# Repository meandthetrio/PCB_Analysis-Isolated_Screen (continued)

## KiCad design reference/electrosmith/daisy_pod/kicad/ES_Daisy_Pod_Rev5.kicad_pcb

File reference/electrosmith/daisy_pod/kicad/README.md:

Converted from `../ES_Daisy_Pod_Rev5.brd` (Eagle 9.6.2) with KiCad 9.0.9's Eagle importer via the `pcbnew` Python API, after stripping 115 Eagle layer definitions the headless importer cannot map (custom/legacy layers such as 17 Pads, 18 Vias, 23/24 Origins, 37/38 Test, 41-47 Restrict/Drills/Holes/Milling/Measures, 53-60, 88-132, 144-255) and the 15 non-copper objects that lived on them. Copper, outline, silk, mask, paste, keepout and documentation layers are untouched. GND zones were filled in KiCad (Eagle's fill is not stored in the .brd). Use this file for DRC and geometry; the .brd stays the source of record.

**Known conversion losses (from the review, `analysis/daisy_pod/PASS1_FAB_CONSTRAINTS.md`):** the two 0.70 × 1.38 mm milled slots for the Molex 47589 board-lock legs (Eagle Milling layer 46) are absent from this file, its Gerbers and drill; the fiducials' tRestrict diamonds are gone, so KiCad's fill touches their mask windows (6 false mask-bridge errors); the vRestrict rings around H1–H4 are gone; the project file carries KiCad default rules, not Electrosmith's `ES_DRC_MaskedVias` set. Eagle's 0.0762 mm per-pad mask frame did survive. Do not fabricate from this conversion.

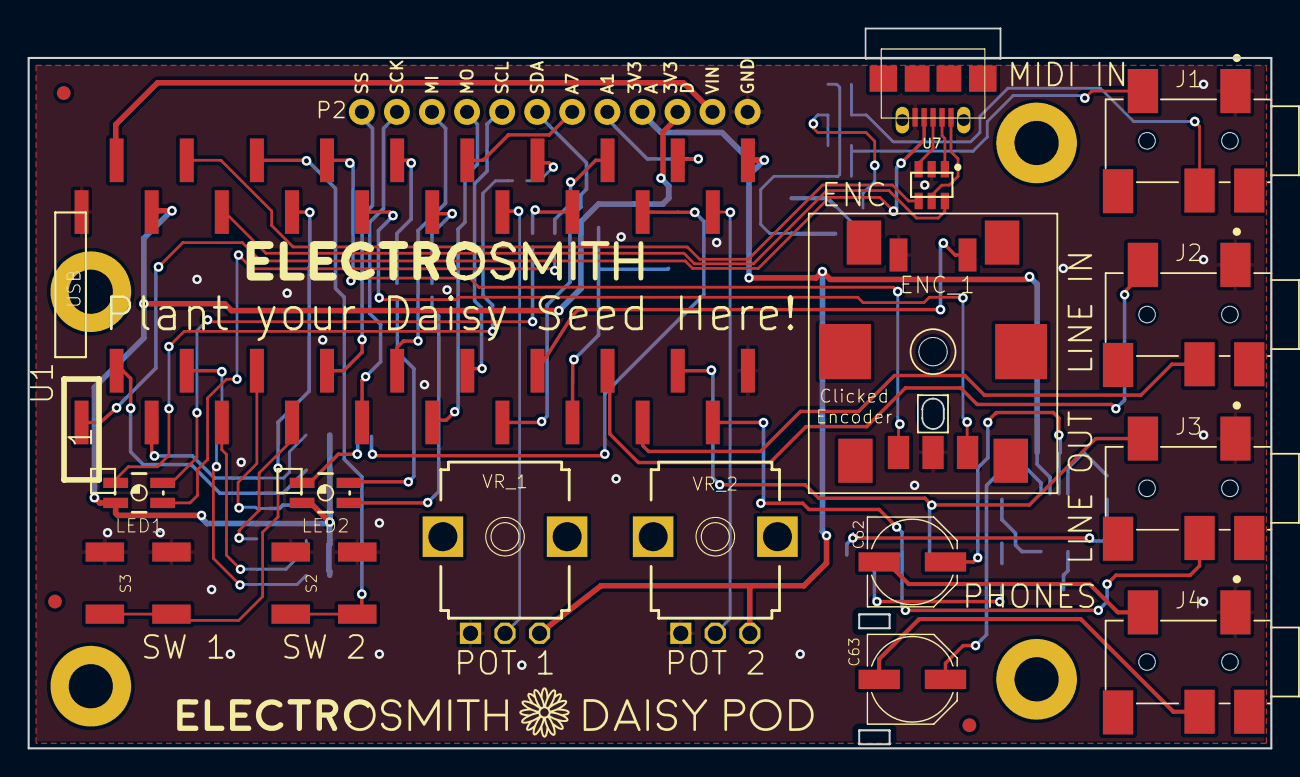
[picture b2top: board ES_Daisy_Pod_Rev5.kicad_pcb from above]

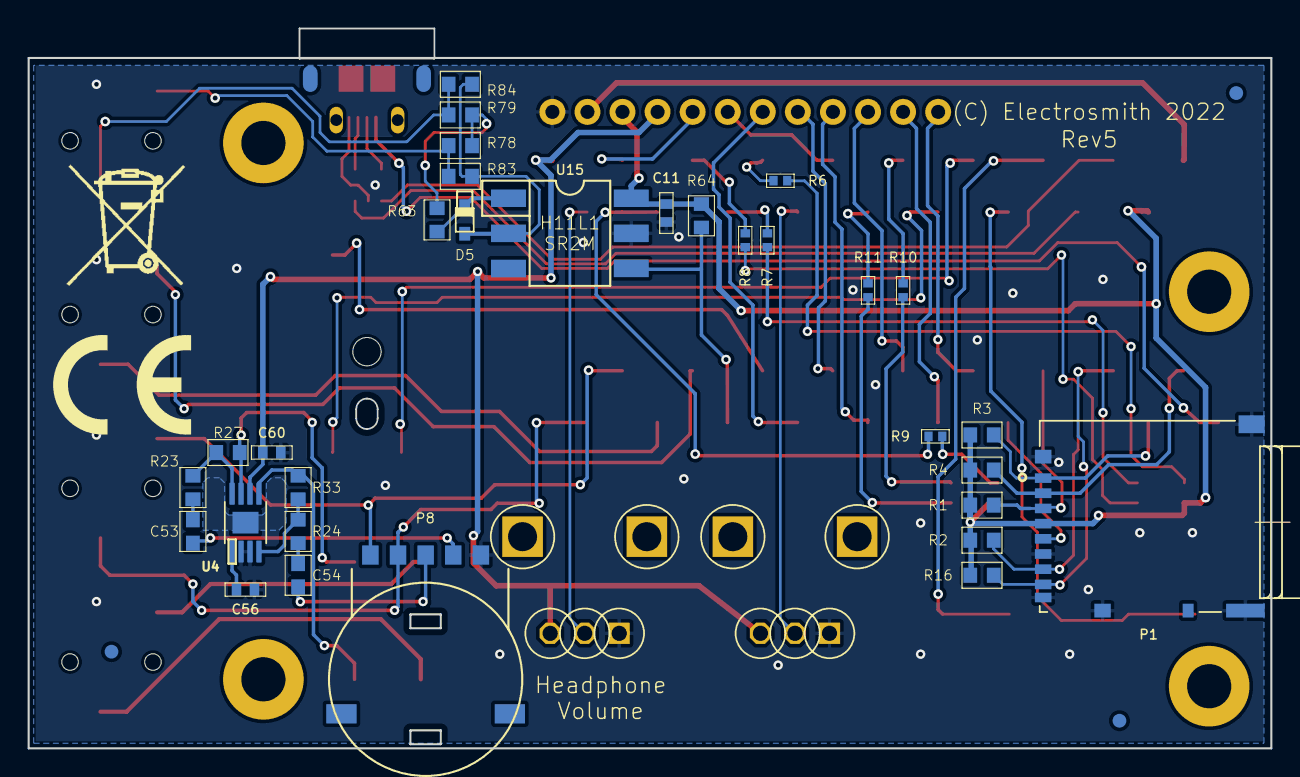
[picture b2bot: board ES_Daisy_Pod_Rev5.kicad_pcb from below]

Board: 2 copper layers, 90.0 x 52.1 mm, 62 parts (36 on the bottom side), 64 nets.

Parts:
C11, C56, C60: 100NF; C0402
C53, C54: 470NF; C0603
C62, C63: 100UF PANASONIC D8; PANASONIC_D
D5: NSR1020MW2T3G; SOD-323F
ENC_1: PEC11 Clicked Encoder; VH1-147
FD1, FD2, FD3, FD4, FD5, FD6: FIDUCIAL; FIDUCIAL_1MM
H1, H2, H3, H4: MOUNT-PAD-ROUND_3.2_NO_SILK; 32-PAD_NO_SILK
J1, J2, J3, J4: SMT Stereo 3.5mm Jack; CUI_SJ2-35863B1-SMT-TR
LED1, LED2: RGB LED SMT PLCC4; P-LCC-4-3
P1: SMT MICRO SD HORIZONTAL; HRS_DM3AT-SF-PEJM5
P2: M12_ALL_CIRCLE_DNI; 1X12_NO_SILK_ALL_CIRCLE
P5: USB MICRO SMT H-B; 47589-0001_CUT2
P8: SMT ROTARY DUAL GANG POT; RK10J12R0A0B
R1, R2, R3, R4, R16: 47K; R0603
R6, R7, R8, R9, R10, R11: 1K; R0402
R23, R24: 22K; R0603
R27, R33: 33K; R0603
R63: 220R; R0603
R64: 270R; R0603
R78, R84: DNI 0R; R0603
R79, R83: 0R; R0603
S2, S3: SMT Mini Button; TL3301SPF160QJ
U1: ES_DAISY_SEED_REV4_SMT; ES_DAISY_SEED_SMT
U4: TPA6110 MSOP-8; MSOP_8_PWRPAD
U7: USBLC6 TVS SOT-23-6; SOT-23-6L
U15: H11L1SR2M; DIL06_GULLWING
U$2: TONNE_9X13MM
U$3: CE_10X7.3MM
U$4: DAISY_POD_BRANDING_2
U$7: ES_TEXT_3X30MM
VR_1, VR_2: P-10K-B-R-PIP; 9MM_SNAP-IN_POT_SILK_PIP

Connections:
+3V3_A: C60.2, P2.9, U1.21, U4.6, VR_1.3, VR_2.3
+3V3_D: C11.1, LED1.2, LED2.2, P1.4, P2.10, R1.2, R2.2, R3.2, R4.2, R16.2, R64.1, U1.38, U15.6
A1: P2.8, U1.23
A7: P2.7, U1.29
AUDIO_IN_L: J2.2, U1.16
AUDIO_IN_R: J2.3, U1.17
AUDIO_OUT_L: J3.2, P8.P$5, U1.18
AUDIO_OUT_R: J3.3, P8.P$4, U1.19
ENC_A: ENC_1.A, U1.33
ENC_B: ENC_1.B, U1.32
ENC_CLICK: ENC_1.E, U1.14
GND: C11.2, C56.1, C60.1, ENC_1.C, ENC_1.D, J1.1, J2.1, J3.1, J4.1, P1.6, P1.P1, P1.P2, P1.P3, P1.P4, P1.SWB, P2.12, P5.5, P8.P$1, S2.3, S2.4, S3.3, S3.4, U1.20, U1.40, U4.2, U4.3, U4.9, U7.2, U15.5, VR_1.1, VR_2.1
HEADPHONE_OUT_L: C62.-, J4.2
HEADPHONE_OUT_R: C63.-, J4.3
HEADPHONE_WIPER_L: C53.1, P8.P$2
HEADPHONE_WIPER_R: C54.1, P8.P$3
I2C_SCL: P2.5, U1.12
I2C_SDA: P2.6, U1.13
LED_1_B: R8.2, U1.25
LED_1_G: R7.2, U1.26
LED_1_R: R6.2, U1.27
LED_2_B: R11.2, U1.30
LED_2_G: R10.2, U1.31
LED_2_R: R9.2, U1.24
MIDI_IN_A: R63.2, R78.1, R79.1
MIDI_IN_B: D5.A, R83.1, R84.1, U15.2
MIDI_IN_RING: J1.3, R79.2, R84.2
MIDI_IN_TIP: J1.2, R78.2, R83.2
unnamed: LED1.1, R6.1
unnamed: LED1.4, R7.1
unnamed: LED1.3, R8.1
unnamed: LED2.1, R9.1
unnamed: LED2.4, R10.1
unnamed: LED2.3, R11.1
unnamed: C54.2, R24.2
unnamed: R23.1, R27.2, U4.8
unnamed: R24.1, R33.2, U4.4
unnamed: C53.2, R23.2
unnamed: C56.2, U4.1
unnamed: C62.+, R27.1, U4.7
unnamed: C63.+, R33.1, U4.5
unnamed: D5.C, R63.1, U15.1
POT_1: U1.28, VR_1.2
POT_2: U1.22, VR_2.2
SD_CK: P1.5, U1.7
SD_CMD: P1.3, R1.1, U1.6
SD_D0: P1.7, R2.1, U1.5
SD_D1: P1.8, R16.1, U1.4
SD_D2: P1.1, R3.1, U1.3
SD_D3: P1.2, R4.1, U1.2
SPI_MISO: P2.3, U1.10
SPI_MOSI: P2.4, U1.11
SPI_NSS: P2.1, U1.8
SPI_SCK: P2.2, U1.9
TAC_SWITCH_1: S3.1, S3.2, U1.34
TAC_SWITCH_2: S2.1, S2.2, U1.35
USART1_RX: R64.2, U1.15, U15.4
USB_OTG_FS_D+: U1.37, U7.4
USB_OTG_FS_D-: U1.36, U7.6
USB_OTG_FS_D_IN_+: P5.3, U7.3
USB_OTG_FS_D_IN_-: P5.2, U7.1
USB_OTG_FS_ID: P5.4, U1.1
USB_VBUS: P5.1, U7.5
VIN: P2.11, U1.39

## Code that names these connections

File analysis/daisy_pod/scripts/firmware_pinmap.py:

"""libDaisy Pod pin constants vs the Rev5 schematic. Reads sch_full.json (eagle_sch_full.py), libDaisy src/daisy_pod.cpp
(seed::Dn constants), src/daisy_seed.h (Dn -> STM32 port/pin) and src/hid/midi.cpp (MIDI UART default pins).
Derives the physical-pin <-> Dn relation from the Seed symbol's own pin names "GPIOn(...)" and checks every constant.
Run: python3 -I firmware_pinmap.py sch_full.json daisy_pod.cpp daisy_seed.h midi.cpp"""
import sys, json, re
sch=json.load(open(sys.argv[1])); pod=open(sys.argv[2]).read(); seedh=open(sys.argv[3]).read(); midi=open(sys.argv[4]).read()
padnet={}
for n,m in sch['nets'].items():
    for x in m: padnet[(x['part'],x['pad'])]=n
u1=sorted(sch['parts']['U1']['pins'],key=lambda p:int(p['pad']))
# physical pin -> Dn from symbol pin name
phys2d={}
for p in u1:
    m=re.match(r'GPIO(\d+)\((.*)\)',p['pin'])
    if m: phys2d[int(p['pad'])]=(int(m.group(1)),m.group(2))
print("physical pin -> D-index relation (from symbol names):")
for pin,(d,fn) in phys2d.items(): print(f"  pin {pin:>2} = D{d:<2} ({fn})  offset {pin-d}")
d2port={int(a):(b,int(c)) for a,b,c in re.findall(r'constexpr Pin D(\d+)\s*=\s*Pin\(PORT([A-K]),\s*(\d+)\)',seedh)}
consts={k:int(v) for k,v in re.findall(r'constexpr Pin (\w+)\s*=\s*seed::D(\d+);',pod.split('/*')[0])}
d2phys={d:pin for pin,(d,_) in phys2d.items()}
expect={'SW_1_PIN':'TAC_SWITCH_1','SW_2_PIN':'TAC_SWITCH_2','ENC_A_PIN':'ENC_A','ENC_B_PIN':'ENC_B','ENC_CLICK_PIN':'ENC_CLICK',
        'LED_1_R_PIN':'LED_1_R','LED_1_G_PIN':'LED_1_G','LED_1_B_PIN':'LED_1_B','LED_2_R_PIN':'LED_2_R','LED_2_G_PIN':'LED_2_G','LED_2_B_PIN':'LED_2_B',
        'KNOB_1_PIN':'POT_1','KNOB_2_PIN':'POT_2'}
print("\nlibDaisy daisy_pod.cpp constant -> Dn -> STM32 -> Seed pin -> schematic net")
ok=True
for k,d in consts.items():
    pin=d2phys[d]; net=padnet[('U1',str(pin))]; port='P%s%d'%d2port[d]
    good=(net==expect.get(k)); ok&=good
    print(f"  {k:<14} D{d:<2} {port:<5} pin {pin:>2} {phys2d[pin][1]:<16} net={net:<14} {'OK' if good else 'MISMATCH (expected '+expect.get(k,'?')+')'}")
m=re.search(r'rx\s*=\s*Pin\(PORT([A-K]),\s*(\d+)\);\s*tx\s*=\s*Pin\(PORT([A-K]),\s*(\d+)\)',midi)
rxp,rxn,txp,txn=m.groups()
port2d={v:k for k,v in d2port.items()}
for lab,(p,n) in (('MIDI rx',(rxp,int(rxn))),('MIDI tx',(txp,int(txn)))):
    d=port2d[(p,n)]; pin=d2phys[d]; print(f"  {lab:<14} D{d:<2} P{p}{n:<4} pin {pin:>2} {phys2d[pin][1]:<16} net={padnet[('U1',str(pin))]}")
# fixed-function pins
for pin in (2,3,4,5,6,7,36,37,1):
    d=phys2d[pin][0]; print(f"  fixed          D{d:<2} P{d2port[d][0]}{d2port[d][1]:<4} pin {pin:>2} {phys2d[pin][1]:<16} net={padnet[('U1',str(pin))]}")
print("\nall Pod constants match:",ok)
